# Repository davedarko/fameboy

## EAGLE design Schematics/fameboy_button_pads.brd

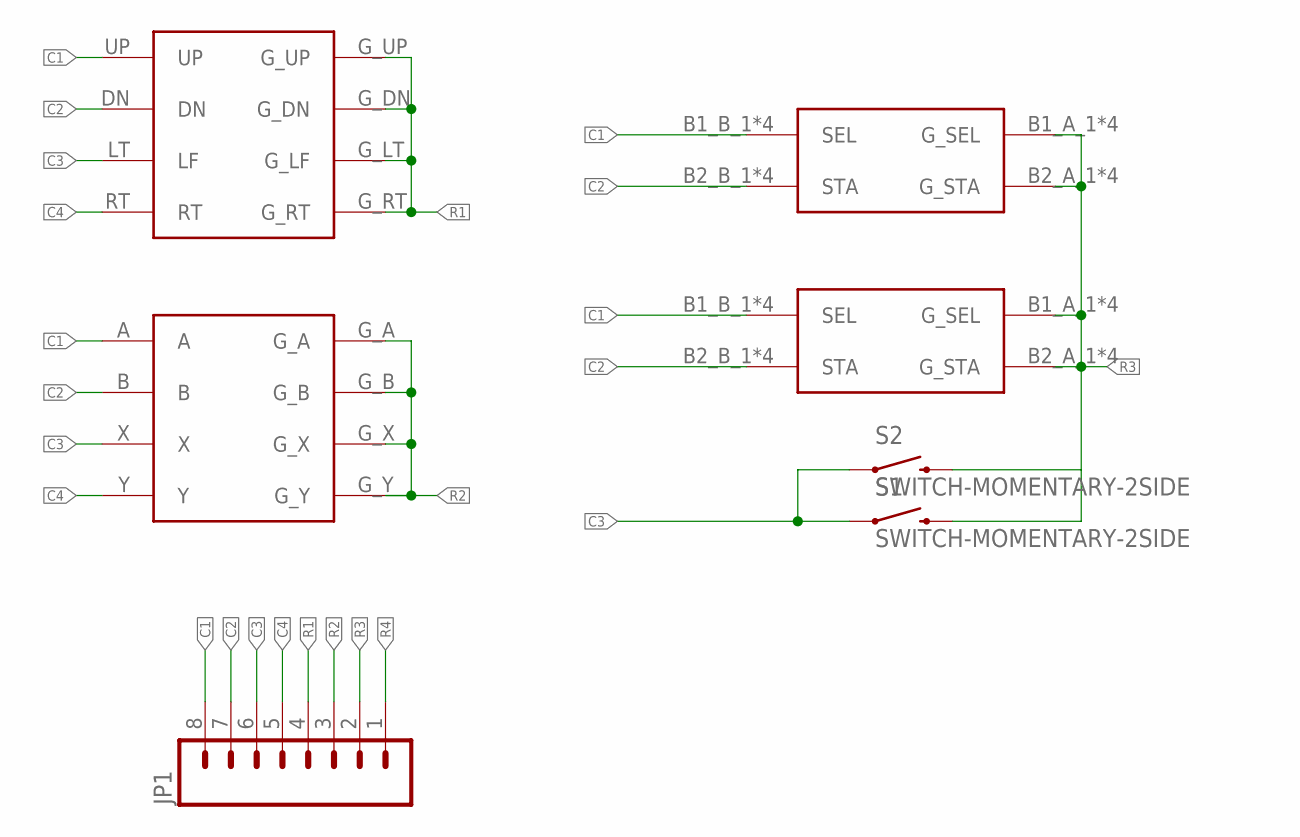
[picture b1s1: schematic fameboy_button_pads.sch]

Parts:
JP1: M08; 1X08_ROUND
S1, S2: SWITCH-MOMENTARY-2SIDE; TACTILE-PTH-SIDE
U$1: DPADGAMEBOY_CLASSIC_DPAD; DPAD
U$2: BAXY; ABXY
U$3, U$4: SELECTSTART

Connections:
C1: JP1.8, U$1.UP, U$2.A, U$3.B1_B_1 (SEL), U$3.B1_B_2 (SEL), U$3.B1_B_3 (SEL), U$3.B1_B_4 (SEL), U$4.B1_B_1 (SEL), U$4.B1_B_2 (SEL), U$4.B1_B_3 (SEL), U$4.B1_B_4 (SEL)
C2: JP1.7, U$1.DN, U$2.B, U$3.B2_B_1 (STA), U$3.B2_B_2 (STA), U$3.B2_B_3 (STA), U$3.B2_B_4 (STA), U$4.B2_B_1 (STA), U$4.B2_B_2 (STA), U$4.B2_B_3 (STA), U$4.B2_B_4 (STA)
C3: JP1.6, S1.1, S2.1, U$1.LT (LF), U$2.X
C4: JP1.5, U$1.RT, U$2.Y
R1: JP1.4, U$1.G_DN, U$1.G_LT (G_LF), U$1.G_RT, U$1.G_UP
R2: JP1.3, U$2.G_A, U$2.G_B, U$2.G_X, U$2.G_Y
R3: JP1.2, S1.2, S2.2, U$3.B1_A_1 (G_SEL), U$3.B1_A_2 (G_SEL), U$3.B1_A_3 (G_SEL), U$3.B1_A_4 (G_SEL), U$3.B2_A_1 (G_STA), U$3.B2_A_2 (G_STA), U$3.B2_A_3 (G_STA), U$3.B2_A_4 (G_STA), U$4.B1_A_1 (G_SEL), U$4.B1_A_2 (G_SEL), U$4.B1_A_3 (G_SEL), U$4.B1_A_4 (G_SEL), U$4.B2_A_1 (G_STA), U$4.B2_A_2 (G_STA), U$4.B2_A_3 (G_STA), U$4.B2_A_4 (G_STA)
R4: JP1.1

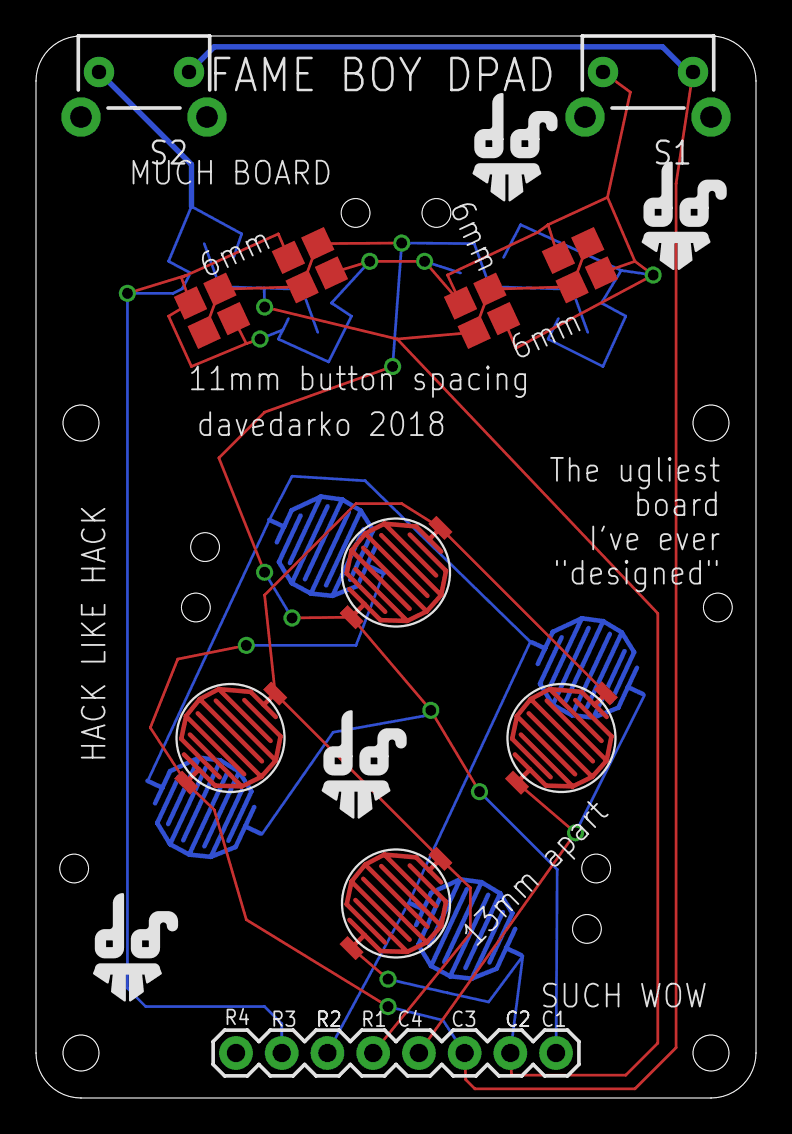
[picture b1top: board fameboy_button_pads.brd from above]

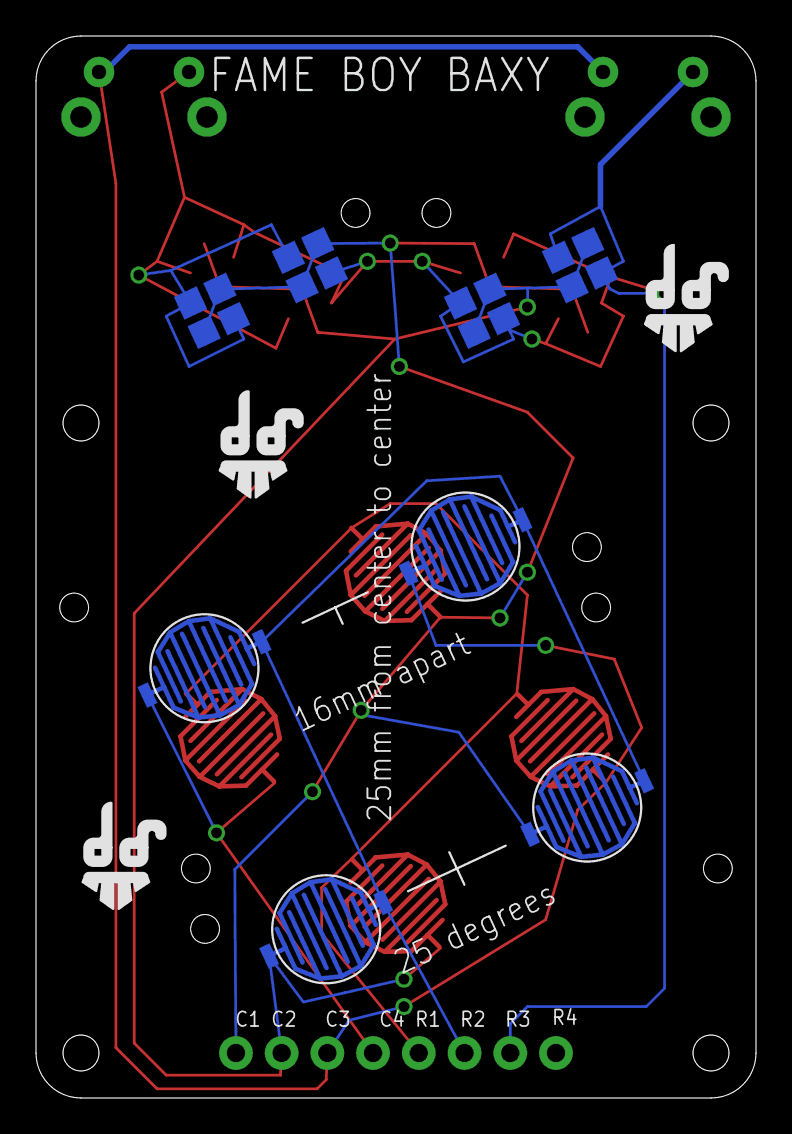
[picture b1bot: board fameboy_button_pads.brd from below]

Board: 2 copper layers, 40.0 x 59.0 mm, 14 parts (5 on the bottom side), 7 nets.

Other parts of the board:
U$5, U$6, U$7, U$8, U$9, U$10, U$11: DAVEDARKO2_LOGO

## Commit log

2018-03-11 probably the ugliest boards I've ever designed
2018-03-11 gerbers
2018-03-13 double shoulder button
2018-03-13 labels
2018-03-17 123D Design

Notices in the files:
parts and their libraries:
SparkFun-Electromechanical: Licensing: Creative Commons ShareAlike 4.0 International - https://creativecommons.org/licenses/by-sa/4.0
